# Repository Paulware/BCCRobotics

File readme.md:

<html>
<body>
<h1>BCC Robotics</h1>
<h2>We will build 3 lego-compatible projects using legos and <a href="https://microbit.org/">micro-bit</a> electronics</h2>
<h3>Car</h2>
<br>
<br>
<br>

<h2>Spider</h2>
<br>
<br>
<a href="https://www.youtube.com/watch?v=a6OLxZTac7w">video</a><br>
<h2>Project 3 Biped</h2>
<br>
<a href="https://youtu.be/c7Dsrjii4ow">video</a><br>
<br>
<h2>Make your own micro-bit compatible device</h2>
<br>
<br>
<br>
<h1>Wiki</h1>
<a href="https://paulware.github.io/BCCRobotics/">Lesson Plan</a>
<br>
</body>
</html>

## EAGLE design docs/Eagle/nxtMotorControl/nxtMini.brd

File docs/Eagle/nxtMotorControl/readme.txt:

1/5/2021
   Initial Creation
1/14/2021
   RJ12 is wrong yo

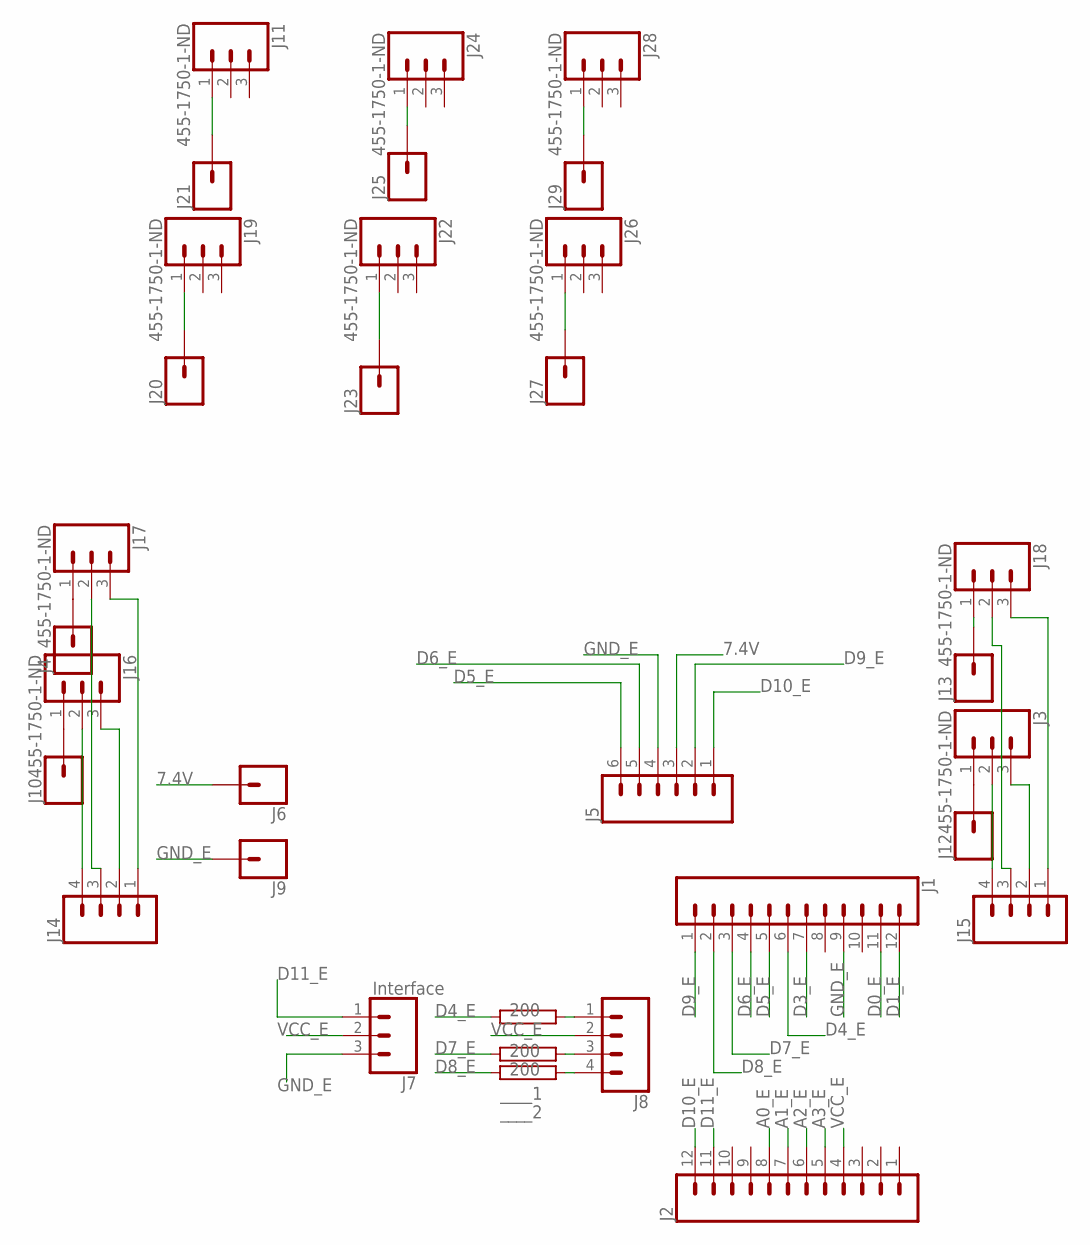
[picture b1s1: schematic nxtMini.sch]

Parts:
200: RCA0001; CA0001
J1, J2: CONN_12; 1X12
J3, J11, J16, J17, J18, J19, J22, J24, J26, J28: 455-1750-1-ND; 1X03
J4, J6, J9, J10, J12, J13, J20, J21, J23, J25, J27, J29: CONN_01; 1X01
J5: CONN_06SILK_FEMALE_PTH; 1X06
J7: Interface; 1X03
J8, J14, J15: CONN_04; 1X04
____1, ____2: 200; CA0001

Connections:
7.4V: J5.3, J6.1
A0_E: J2.8
A1_E: J2.7
A2_E: J2.6
A3_E: J2.5
D0_E: J1.11
D1_E: J1.12
D3_E: J1.7
D4_E: 200.1, J1.6
D5_E: J1.5, J5.6
D6_E: J1.4, J5.5
D7_E: J1.3, ____1.1
D8_E: J1.2, ____2.1
D9_E: J1.1, J5.2
D10_E: J2.12, J5.1
D11_E: J2.11, J7.1
GND_E: J1.9, J5.4, J7.3, J9.1
unnamed: J4.1, J17.1
unnamed: J10.1, J16.1
unnamed: 200.2, J8.1
unnamed: J8.3, ____1.2
unnamed: J8.4, ____2.2
unnamed: J3.1, J12.1
unnamed: J13.1, J18.1
unnamed: J14.4, J16.2
unnamed: J14.3, J17.2
unnamed: J14.2, J16.3
unnamed: J14.1, J17.3
unnamed: J3.2, J15.4
unnamed: J15.3, J18.2
unnamed: J3.3, J15.2
unnamed: J15.1, J18.3
unnamed: J19.1, J20.1
unnamed: J11.1, J21.1
unnamed: J22.1, J23.1
unnamed: J24.1, J25.1
unnamed: J26.1, J27.1
unnamed: J28.1, J29.1
VCC_E: J2.4, J7.2, J8.2

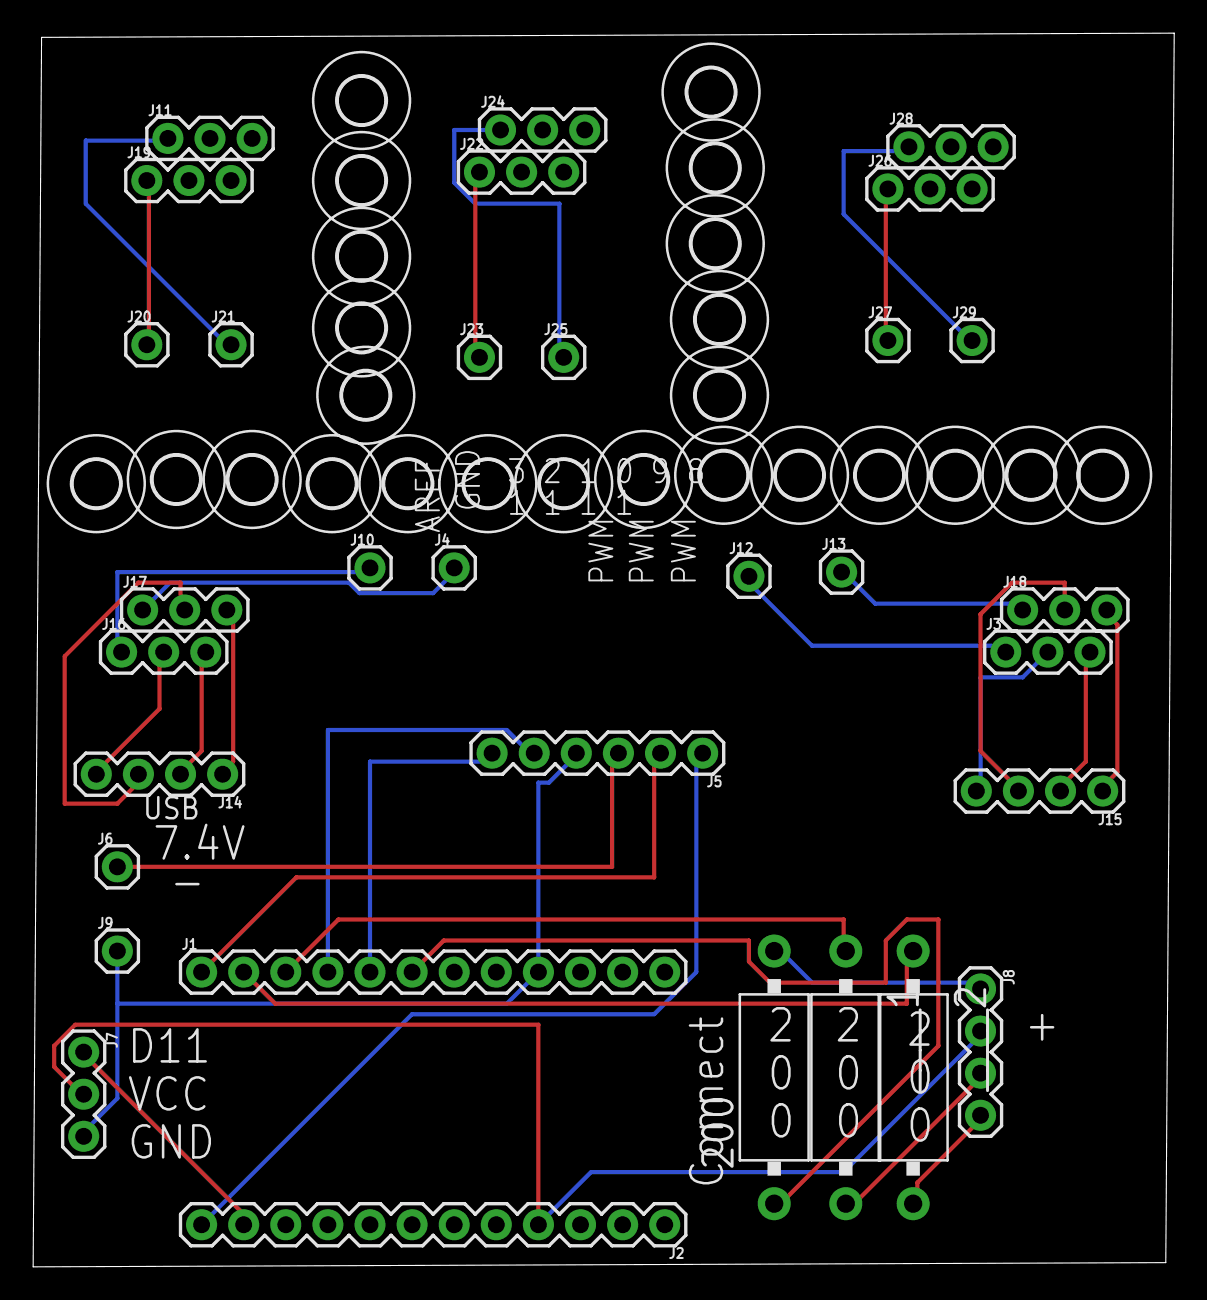
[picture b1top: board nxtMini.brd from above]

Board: 2 copper layers, 68.8 x 74.4 mm, 56 parts (0 on the bottom side), 32 nets.

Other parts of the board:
U$1, U$2, U$3, U$4, U$5, U$6, U$7, U$8, U$9, U$10, U$11, U$12, U$13, U$14, U$15, U$16, U$17, U$18, U$19, U$20, U$21, U$22, U$23, U$24: 2,8

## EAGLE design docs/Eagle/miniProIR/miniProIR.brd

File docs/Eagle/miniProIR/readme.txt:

1/5/2021
   Add a tri-color LED
1/7/2021  
   Made smaller footprint, ordered
1/18/2021  
   + mark on board is incorrect for LED
   did not order

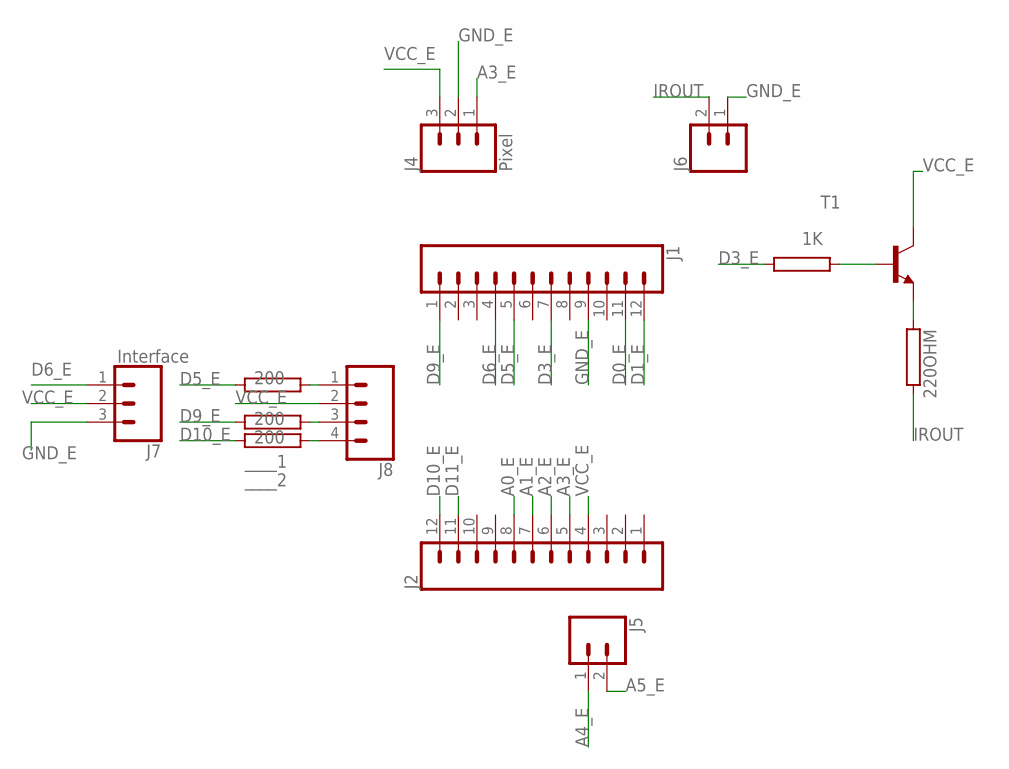
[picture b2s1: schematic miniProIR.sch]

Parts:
1K, 200, 220OHM: RCA0001; CA0001
J1, J2: CONN_12; 1X12
J4: Pixel; 1X03
J5, J6: CONN_02; 1X02
J7: Interface; 1X03
J8: CONN_04; 1X04
T1: 29-NPN-TO92-EBC; TO92-EBC
____1, ____2: 200; CA0001

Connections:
A0_E: J2.8
A1_E: J2.7
A2_E: J2.6
A3_E: J2.5, J4.1
A4_E: J5.1
A5_E: J5.2
D0_E: J1.11
D1_E: J1.12
D3_E: 1K.1, J1.7
D5_E: 200.1, J1.5
D6_E: J1.4, J7.1
D9_E: J1.1, ____1.1
D10_E: J2.12, ____2.1
D11_E: J2.11
GND_E: J1.9, J4.2, J6.1, J7.3
IROUT: 220OHM.2, J6.2
unnamed: 220OHM.1, T1.E
unnamed: 1K.2, T1.B
unnamed: 200.2, J8.1
unnamed: J8.3, ____1.2
unnamed: J8.4, ____2.2
VCC_E: J2.4, J4.3, J7.2, J8.2, T1.C

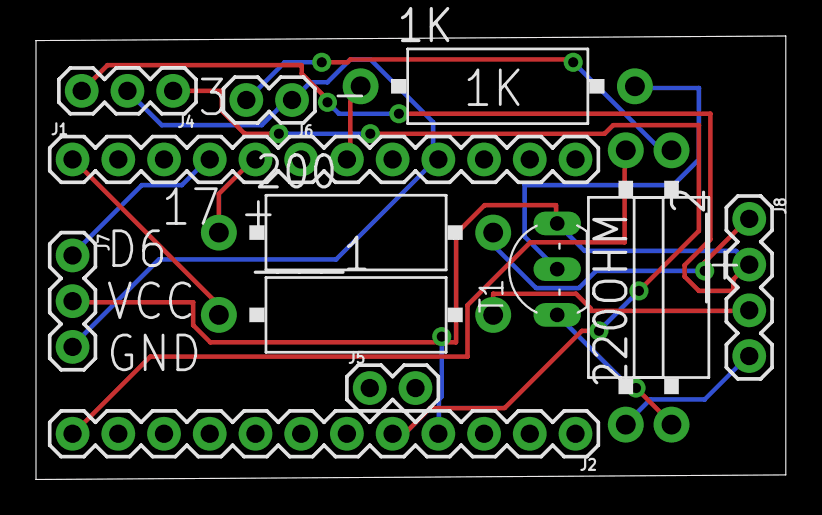
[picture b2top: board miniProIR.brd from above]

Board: 2 copper layers, 41.7 x 24.6 mm, 13 parts (0 on the bottom side), 14 nets.

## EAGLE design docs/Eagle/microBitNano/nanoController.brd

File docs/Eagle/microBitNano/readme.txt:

1/4/2021
   Added RGB led
1/4/2021  
   Detected issue with D11/D12
   Added on/off power jumper
   Add hbridge connector
   power jumper to power switch
1/14/2021  
   Power switch turns off power to voltage regulator
   Removed ir
   Added a diode between power nano and 3.3V line
   Add a button
   ordered 3:42 PM

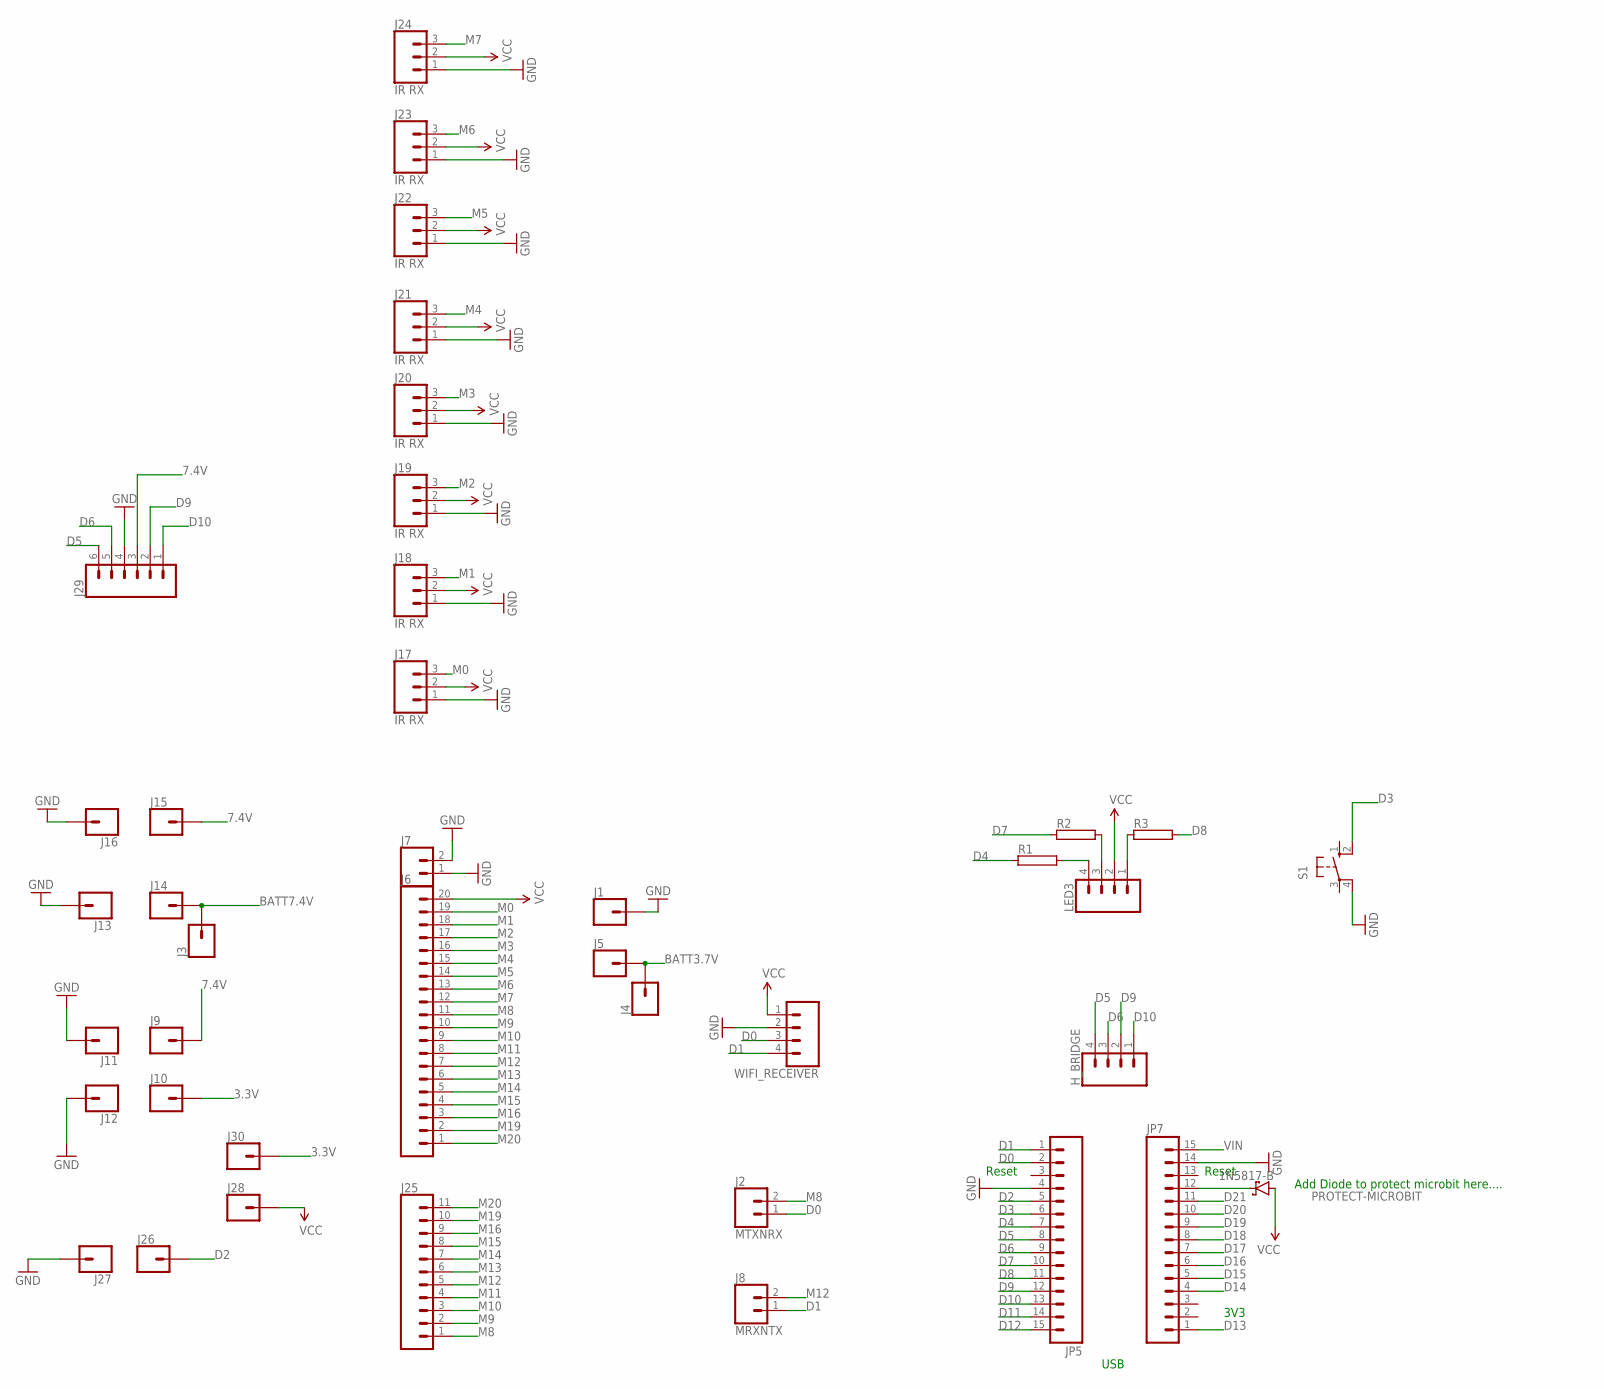
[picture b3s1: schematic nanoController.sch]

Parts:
H_BRIDGE: CONN_04LONGPADS; 1X04_LONGPADS
J1, J5: CONN_01SMTSO-256-ET-0.165DIA; SMTSO-256-ET-0.165DIA
J2: MTXNRX; 1X02
J3, J4, J9, J10, J11, J12, J13, J14, J15, J16, J26, J27, J28, J30: CONN_01; 1X01
J6: CONN_20; 1X20
J7: CONN_02; 1X02
J8: MRXNTX; 1X02
J17, J18, J19, J20, J21, J22, J23, J24: IR RX; 1X03
J25: CONN_11; 1X11
J29: CONN_06SILK_FEMALE_PTH; 1X06
JP5, JP7: M15; 1X15
LED3: CONN_04LONGPADS; 1X04_LONGPADS
PROTECT-MICROBIT: 1N5817-B; DO41-7.6
R1, R2, R3: RHPS58; HPS58
S1: 10-XX; B3F-10XX
WIFI_RECEIVER: CONN_04LONGPADS; 1X04_LONGPADS

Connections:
3.3V: J10.1, J30.1
7.4V: J9.1, J15.1, J29.3
BATT3.7V: J4.1, J5.P$1
BATT7.4V: J3.1, J14.1
D0: J2.1, JP5.2, WIFI_RECEIVER.3
D1: J8.1, JP5.1, WIFI_RECEIVER.4
D2: J26.1, JP5.5
D3: JP5.6, S1.2 (S1)
D4: JP5.7, R1.1
D5: H_BRIDGE.4, J29.6, JP5.8
D6: H_BRIDGE.3, J29.5, JP5.9
D7: JP5.10, R2.1
D8: JP5.11, R3.2
D9: H_BRIDGE.2, J29.2, JP5.12
D10: H_BRIDGE.1, J29.1, JP5.13
D11: JP5.14
D12: JP5.15
D13: JP7.1
D14: JP7.4
D15: JP7.5
D16: JP7.6
D17: JP7.7
D18: JP7.8
D19: JP7.9
D20: JP7.10
D21: JP7.11
GND: J1.P$1, J7.1, J7.2, J11.1, J12.1, J13.1, J16.1, J17.1, J18.1, J19.1, J20.1, J21.1, J22.1, J23.1, J24.1, J27.1, J29.4, JP5.4, JP7.14, S1.4 (P1), WIFI_RECEIVER.2
M0: J6.19, J17.3
M1: J6.18, J18.3
M2: J6.17, J19.3
M3: J6.16, J20.3
M4: J6.15, J21.3
M5: J6.14, J22.3
M6: J6.13, J23.3
M7: J6.12, J24.3
M8: J2.2, J6.11, J25.1
M9: J6.10, J25.2
M10: J6.9, J25.3
M11: J6.8, J25.4
M12: J6.7, J8.2, J25.5
M13: J6.6, J25.6
M14: J6.5, J25.7
M15: J6.4, J25.8
M16: J6.3, J25.9
M19: J6.2, J25.10
M20: J6.1, J25.11
unnamed: LED3.4, R1.2
unnamed: LED3.3, R2.2
unnamed: LED3.1, R3.1
unnamed: JP7.12, PROTECT-MICROBIT.C
VCC: J6.20, J17.2, J18.2, J19.2, J20.2, J21.2, J22.2, J23.2, J24.2, J28.1, LED3.2, PROTECT-MICROBIT.A, WIFI_RECEIVER.1
VIN: JP7.15

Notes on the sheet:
Reset
3V3
USB
Add Diode to protect microbit here....

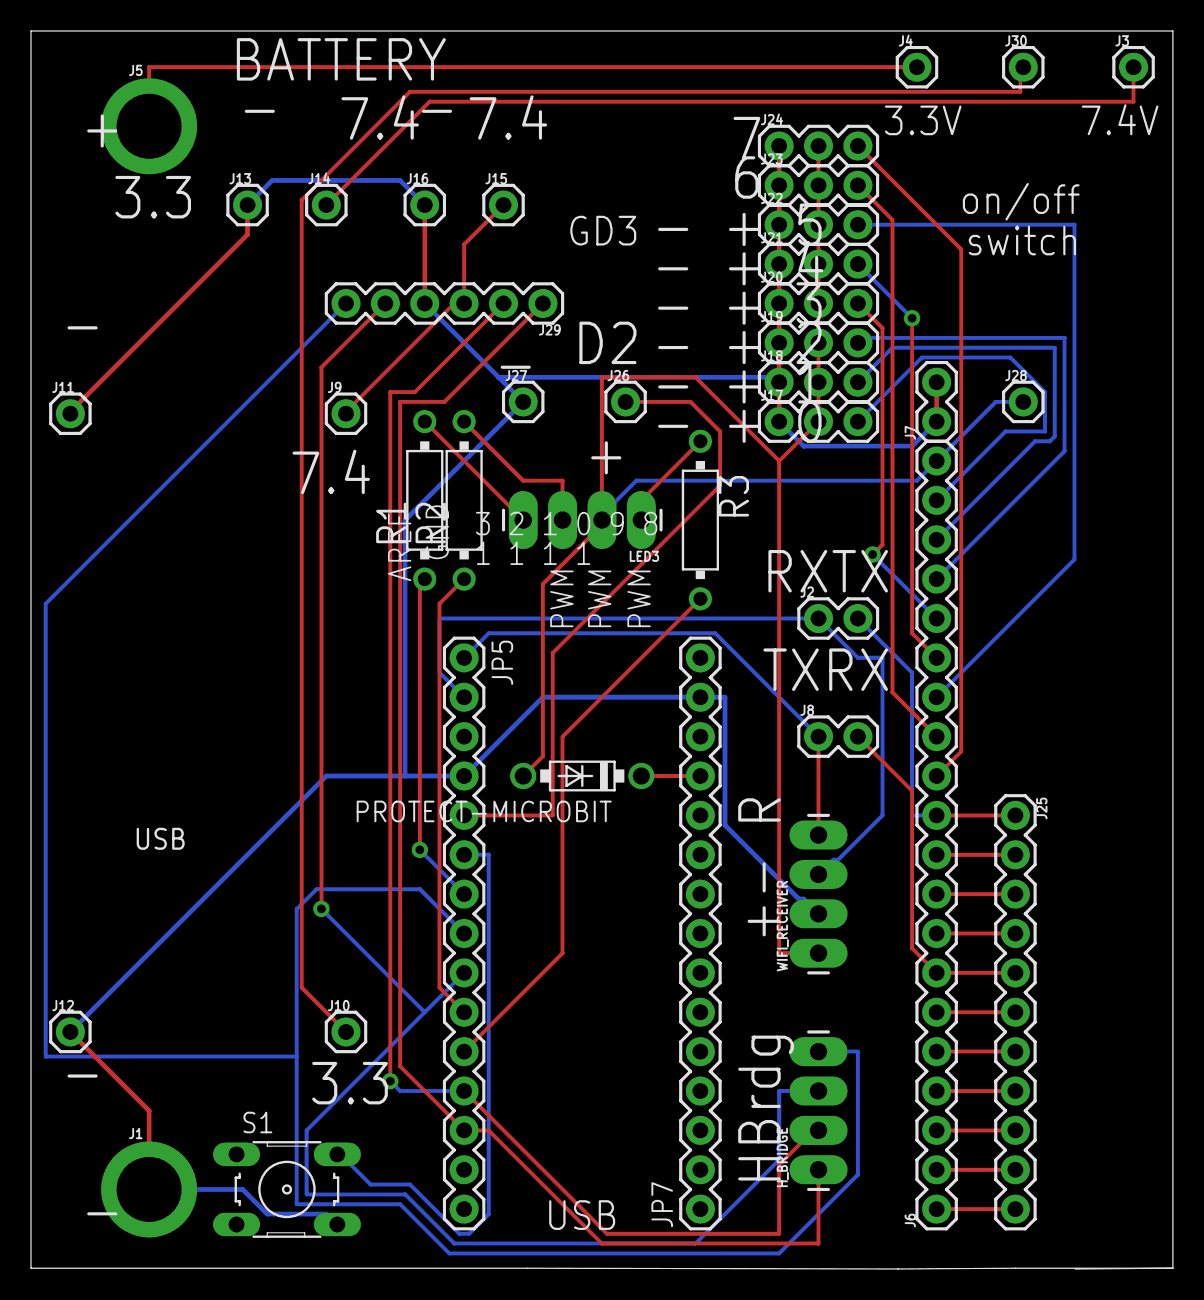
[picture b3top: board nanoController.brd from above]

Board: 2 copper layers, 73.7 x 79.9 mm, 40 parts (0 on the bottom side), 40 nets.

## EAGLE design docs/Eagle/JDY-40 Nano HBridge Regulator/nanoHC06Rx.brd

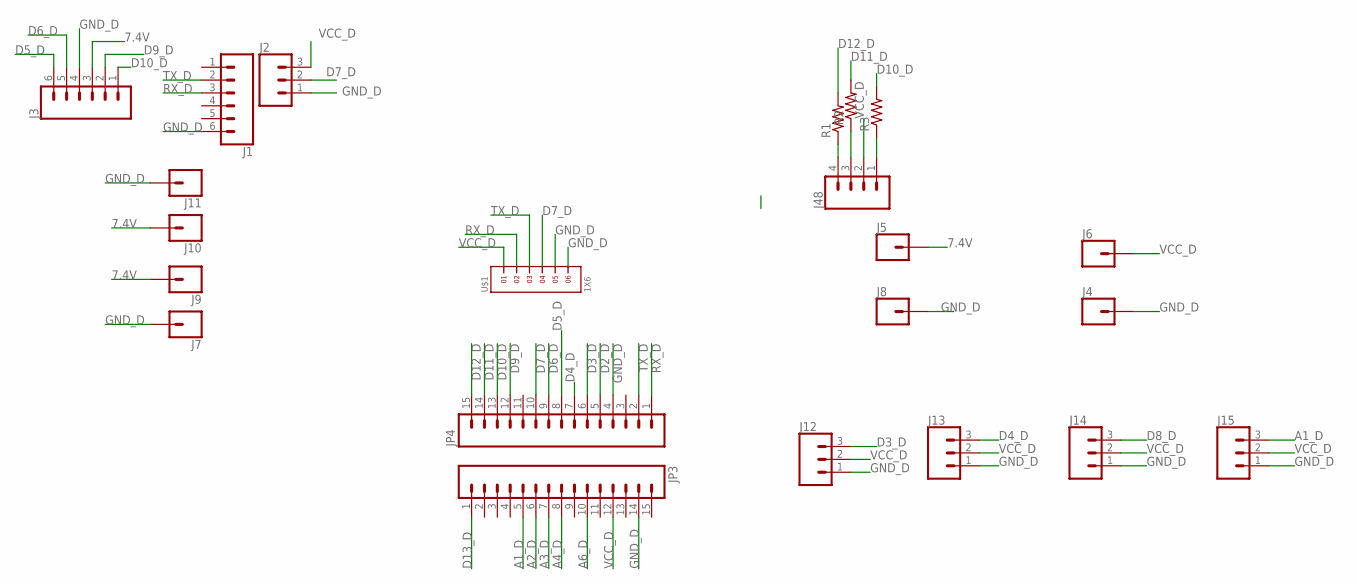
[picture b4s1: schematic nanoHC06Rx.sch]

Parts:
J1, J3: CONN_06SILK_FEMALE_PTH; 1X06
J2, J12, J13, J14, J15: CONN_03; 1X03
J4, J5, J6, J7, J8, J9, J10, J11: CONN_01; 1X01
J48: CONN_04; 1X04
JP3, JP4: M15; 1X15@1
R1, R2, R3: R-US_0309/10; 0309/10
U$1: 1X6

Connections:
7.4V: J3.3, J5.1, J9.1, J10.1
A1_D: J15.3, JP3.5
A2_D: JP3.6
A3_D: JP3.7
A4_D: JP3.8
A6_D: JP3.10
D2_D: JP4.5
D3_D: J12.3, JP4.6
D4_D: J13.3, JP4.7
D5_D: J3.6, JP4.8
D6_D: J3.5, JP4.9
D7_D: J2.2, JP4.10, U$1.4
D8_D: J14.3
D9_D: J3.2, JP4.12
D10_D: J3.1, JP4.13, R3.2
D11_D: JP4.14, R2.2
D12_D: JP4.15, R1.2
D13_D: JP3.1
GND_D: J1.6, J2.1, J3.4, J4.1, J7.1, J8.1, J11.1, J12.1, J13.1, J14.1, J15.1, JP3.14, JP4.4, U$1.5, U$1.6
unnamed: J48.4, R1.1
unnamed: J48.3, R2.1
unnamed: J48.1, R3.1
RX_D: J1.3, JP4.1, U$1.2
TX_D: J1.2, JP4.2, U$1.3
VCC_D: J2.3, J6.1, J12.2, J13.2, J14.2, J15.2, J48.2, JP3.12, U$1.1

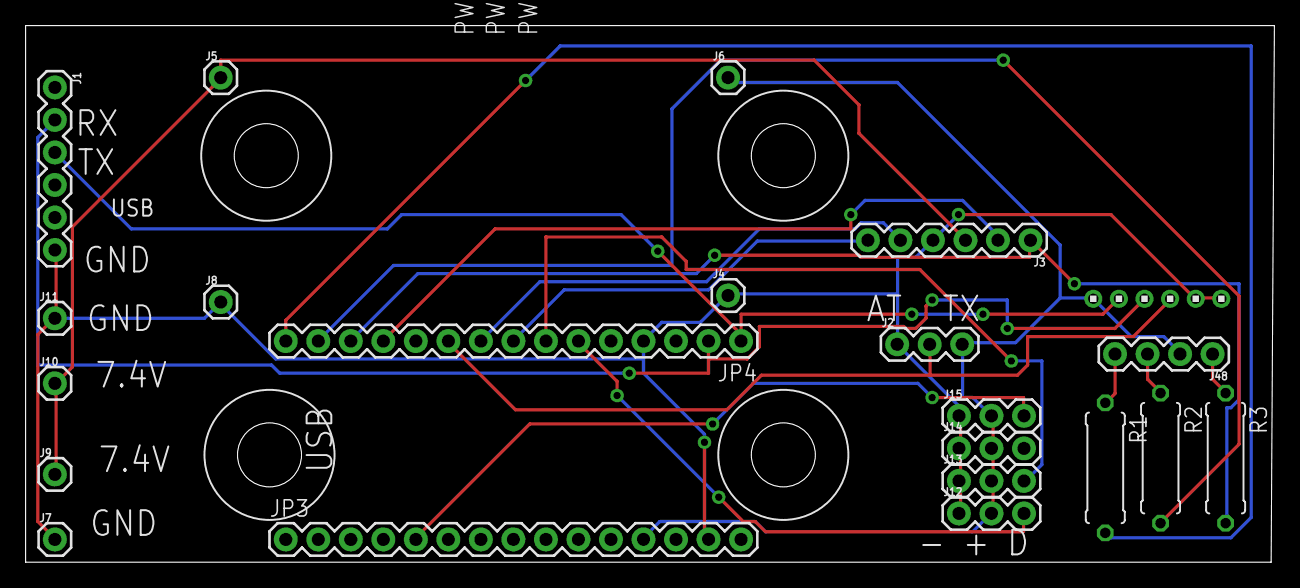
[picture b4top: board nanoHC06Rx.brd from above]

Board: 2 copper layers, 97.5 x 41.9 mm, 26 parts (0 on the bottom side), 18 nets.

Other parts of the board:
U$2, U$3, U$4, U$5: DRIL-5

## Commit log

2020-12-20 images
2020-12-21 spell
2020-12-21 Video
2020-12-21 typo
2020-12-23 Project 1 - Virtual
2020-12-23 Project 2 car and joystick
2020-12-28 project 3'
2020-12-29 readme
2020-12-29 class
2020-12-30 Eagle
2021-01-04 crossover
2021-01-08 Added spider/biped assembly
2021-01-21 music
2021-01-23 list

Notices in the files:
parts and their libraries:
SparkFun-Connectors: Licensing: Creative Commons ShareAlike 4.0 International - https://creativecommons.org/licenses/by-sa/4.0
